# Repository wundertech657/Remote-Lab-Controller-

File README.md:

# Raymond's Remote-Lab-Controller
This is my project for the Hack Club Blueprint. I wanted to build this because I really like chemical engineering, and many times I needed to control my laptop from a safe distance during a reaction, but I couldn’t. I also enjoy engineering in general, and I wanted to try some electrical and software engineering projects to learn more about this part of science.
# How I started the project
As I said, I didn’t have any experience, so I followed the tutorial. I chose a simple setup with two buttons, a rotary encoder, and an OLED screen.

# Schematic
After I figured out how to use KiCAD, I managed to make what I believe is a correct schematic.
# PCB
Here is where the real design started. At this point I had to make a final decision about how to arrange my components and where to place the screen, which is a critical hardware and design element of my macropad.
## 
- The space above the microchip will be translucent
-  next to the encoder the whole design is symmetric and comfortable to hold.
  # 3D Design
  In this part I was already more experienced, but until now I hadn’t really used fully finished component models. At this point I started to get familiar with more precise design and real‑world application. I used Fusion 360 because it fits my experience level and it’s great for accurate design work. When I 3D print the model I will add the joints in Bambu studio
  
## The fully assembled model

- The model from different perspectives

- The case of the macropad

- without the top part
   
     At the end of the modeling process, I made an engineering drawing.

   - Here you can see the model’s dimensions.
  
   # The code
   In this field I am very inexperienced, and I used help to create my firmware. It was written in C++. It’s very likely that it still has some errors, but the main structure and idea are clearly represented in the code.
# List of materials
- Seeed XIAO RP2040
- 2 MX-Style switches
- EC11 Rotary encoder
- 1 PCB
- 0.91 inch OLED displays
- Case[I 3D print it ]
- 2 Cherry MX Keycaps[I 3D print it]

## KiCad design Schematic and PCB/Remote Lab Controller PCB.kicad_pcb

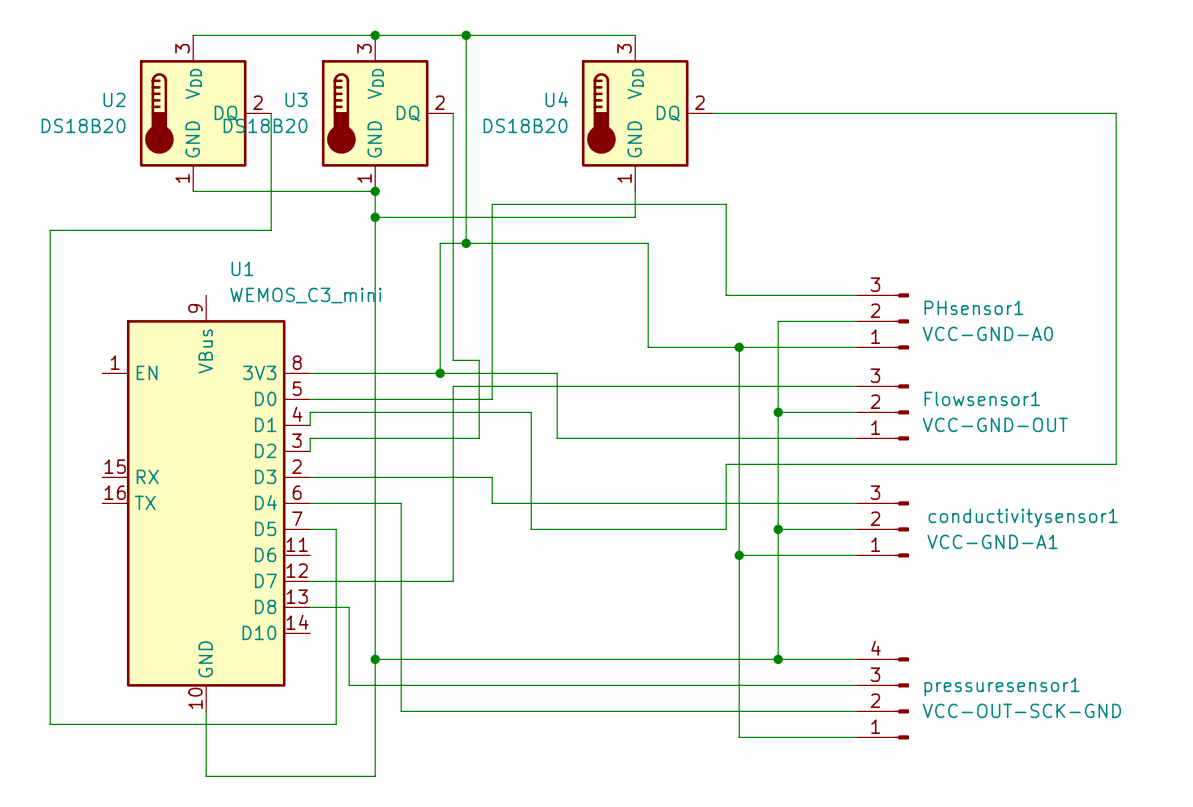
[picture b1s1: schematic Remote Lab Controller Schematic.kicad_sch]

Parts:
Flowsensor1: VCC-GND-OUT; FanPinHeader_1x03_P2.54mm_Vertical
PHsensor1: VCC-GND-A0; FanPinHeader_1x03_P2.54mm_Vertical
U1: WEMOS_C3_mini
U2, U3, U4: DS18B20; TO-92_Inline
conductivitysensor1: VCC-GND-A1; FanPinHeader_1x03_P2.54mm_Vertical
pressuresensor1: VCC-OUT-SCK-GND; FanPinHeader_1x04_P2.54mm_Vertical

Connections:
unnamed: Flowsensor1.1, PHsensor1.1, U1.8 (3V3), U2.3 (V_{DD}), U3.3 (V_{DD}), U4.3 (V_{DD}), conductivitysensor1.1, pressuresensor1.1
unnamed: Flowsensor1.2, PHsensor1.2, U1.10 (GND), U2.1 (GND), U3.1 (GND), U4.1 (GND), conductivitysensor1.2, pressuresensor1.4
unnamed: Flowsensor1.3, U1.12 (D7)
unnamed: PHsensor1.3, U1.5 (D0)
unnamed: U1.4 (D1), U4.2 (DQ)
unnamed: U1.3 (D2), U3.2 (DQ)
unnamed: U1.2 (D3), conductivitysensor1.3
unnamed: U1.6 (D4), pressuresensor1.2
unnamed: U1.7 (D5), U2.2 (DQ)
unnamed: U1.13 (D8), pressuresensor1.3

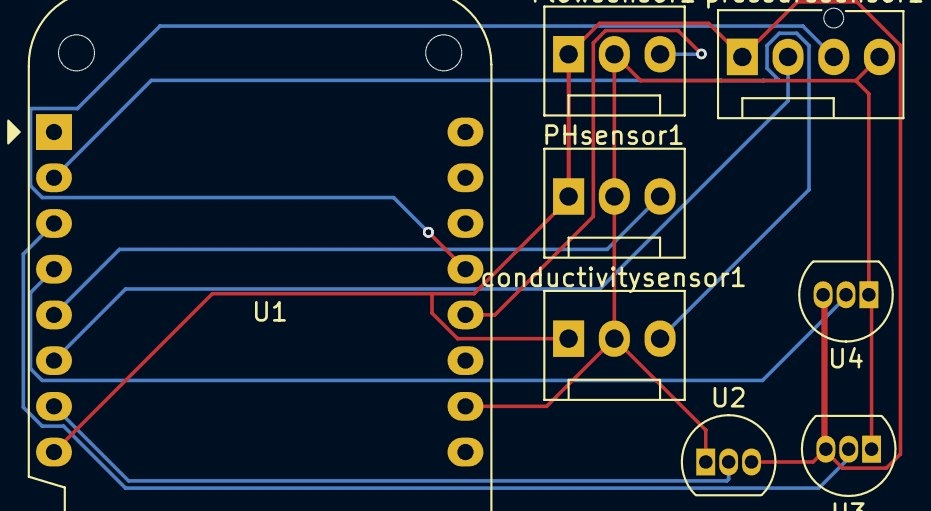
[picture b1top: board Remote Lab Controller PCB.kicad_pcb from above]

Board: 2 copper layers, 8 parts (0 on the bottom side), 10 nets.

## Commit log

2026-01-21 3D models
2026-01-21 Create 3D models
2026-01-21 Create Here are the models
2026-02-23 Create PCB and Schematic
